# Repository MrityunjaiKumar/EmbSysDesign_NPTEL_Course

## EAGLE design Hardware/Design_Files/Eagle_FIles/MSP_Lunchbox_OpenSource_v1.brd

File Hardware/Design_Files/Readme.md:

# Design Files

- [Eagle Files locations ](./Eagle/)

### Schematic file

### Board file

### License
 GPL-3.0 License

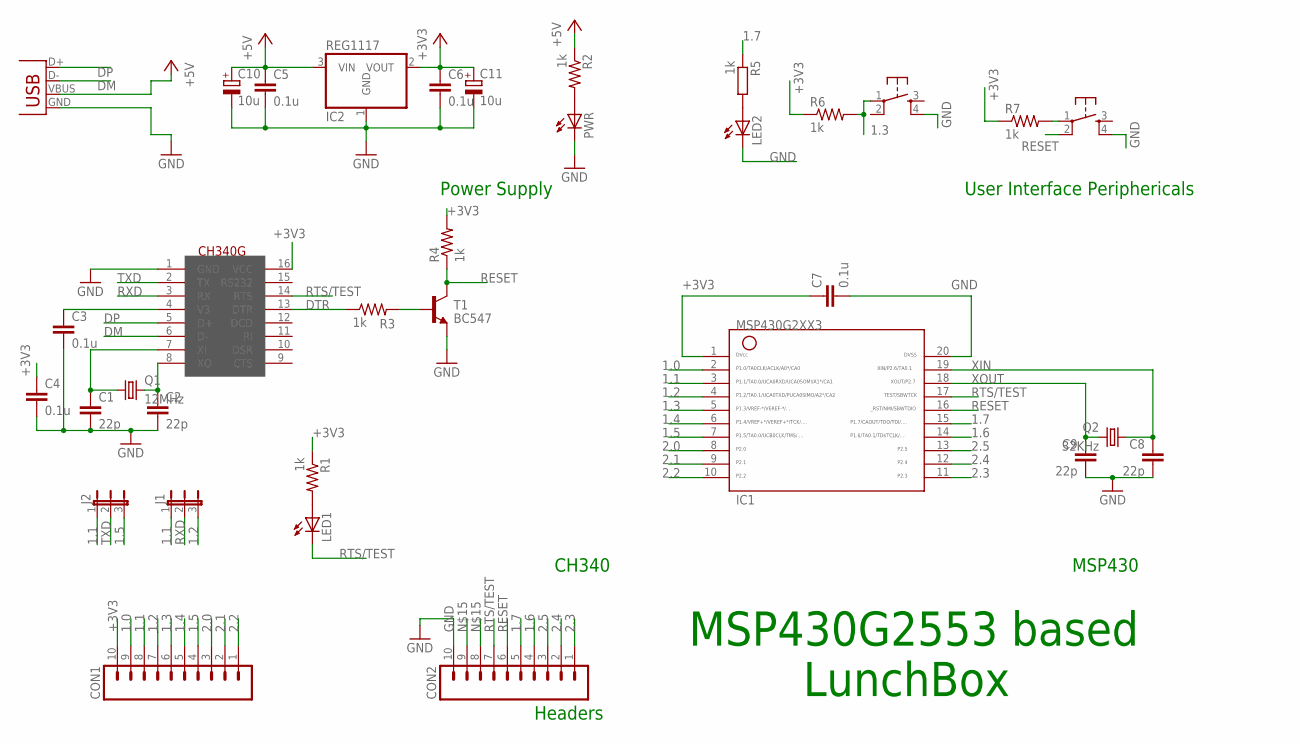
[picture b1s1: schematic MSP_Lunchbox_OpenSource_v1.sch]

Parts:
C1, C2, C8, C9: 22p; C0805
C3, C4, C5, C6: 0.1u; C0805
C7: 0.1u; C075-032X103
C10, C11: 10u; B/3528-21R
CH340: CH340; SOIC16
CON1, CON2: M10; 10P
IC1: MSP430G2553DIP20; G2553-DIP20
IC2: REG1117; SOT223
J1, J2: JP2E; JP2
LED1, LED2: LED3MM
PWR: LED3MM
Q1: 12MHz; HC49US
Q2: 32KHz; TC26H
R1, R2, R3, R4: 1k; 0207/10
R5: 1k; 0207/12
R6, R7: 1k; 0204/7
RESET: OMRON_SWITCH_10-XX; B3F-10XX
SW1: OMRON_SWITCH_10-XX; B3F-10XX
T1: BC547; TO92
X2: USBSMD; USB-MINIB

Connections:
1.0: CON1.9, IC1.2
1.1: CON1.8, IC1.3, J1.1, J2.1
1.2: CON1.7, IC1.4, J1.3
1.3: CON1.6, IC1.5, R6.2, SW1.1
1.4: CON1.5, IC1.6
1.5: CON1.4, IC1.7, J2.3
1.6: CON2.4, IC1.14
1.7: CON2.5, IC1.15, R5.1
2.0: CON1.3, IC1.8
2.1: CON1.2, IC1.9
2.2: CON1.1, IC1.10
2.3: CON2.1, IC1.11
2.4: CON2.2, IC1.12
2.5: CON2.3, IC1.13
+3V3: C4.1, C6.1, C7.1, C11.+, CH340.16 (VCC), CON1.10, IC1.1, IC2.2 (VOUT), R1.1, R4.2, R6.1, R7.1
+5V: C5.1, C10.+, IC2.3 (VIN), R2.1, X2.VBUS
DM: CH340.6 (D-), X2.D-
DP: CH340.5 (D+), X2.D+
DTR: CH340.13 (DTR), R3.1
GND: C1.2, C2.2, C3.2, C4.2, C5.2, C6.2, C7.2, C8.2, C9.2, C10.-, C11.-, CH340.1 (GND), CON2.10, IC1.20, IC2.1 (GND), LED2.K (C), PWR.K (C), RESET.4 (S1), SW1.4 (S1), T1.1 (E), X2.GND
unnamed: LED1.A, R1.2
unnamed: PWR.A, R2.2
unnamed: C1.1, CH340.7 (XI), Q1.1
unnamed: C2.1, CH340.8 (XO), Q1.2
unnamed: LED2.A, R5.2
unnamed: R7.2, RESET.1
unnamed: R3.2, T1.2 (B)
unnamed: C3.1, CH340.4 (V3)
RESET: CON2.6, IC1.16, R4.1, RESET.2 (P1), T1.3 (C)
RTS/TEST: CH340.14 (RTS), CON2.7, IC1.17, LED1.K (C)
RXD: CH340.3 (RX), J1.2
TXD: CH340.2 (TX), J2.2
XIN: C8.1, IC1.19, Q2.1
XOUT: C9.1, IC1.18, Q2.2

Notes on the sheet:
Power Supply
MSP430
Headers
User Interface Periphericals
CH340
MSP430G2553 based
LunchBox

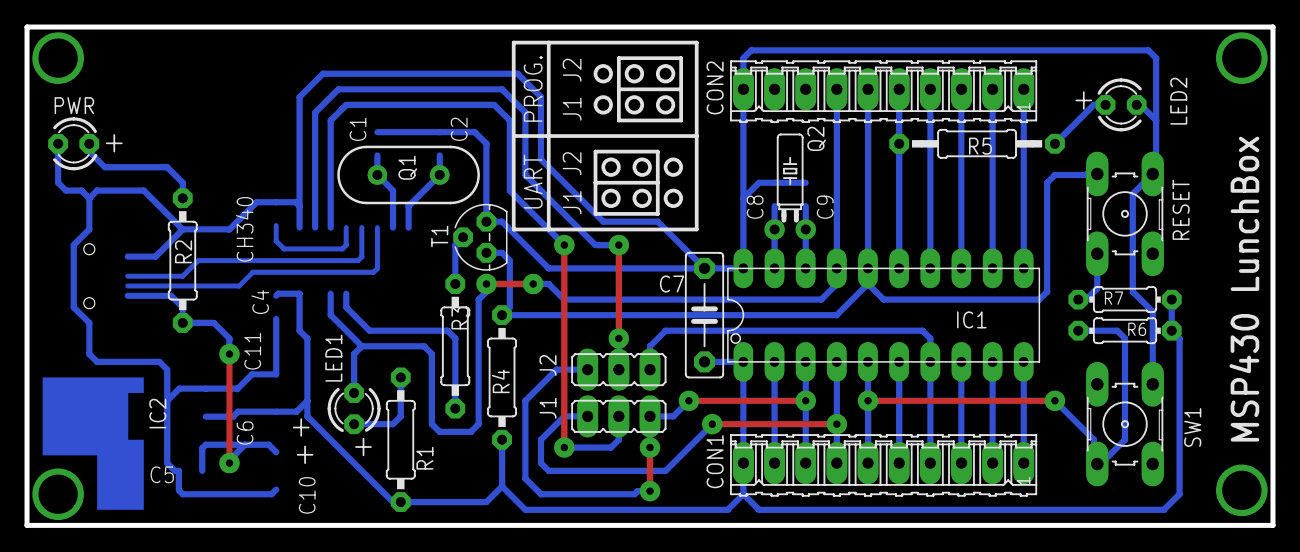
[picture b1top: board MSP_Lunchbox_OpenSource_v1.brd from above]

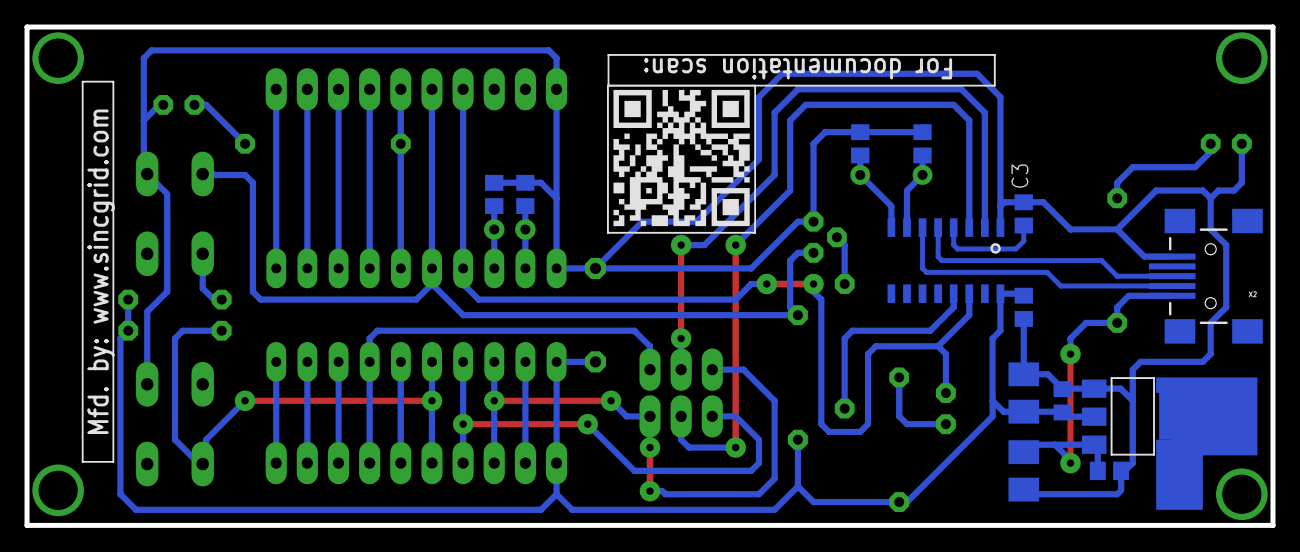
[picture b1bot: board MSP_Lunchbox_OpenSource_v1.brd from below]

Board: 2 copper layers, 101.6 x 40.6 mm, 34 parts (13 on the bottom side), 34 nets.

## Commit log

2020-01-18 Uploaded UART_printf example zip file.
2020-01-20 basic code added
2020-01-20 Exp01_LunchBox_HelloLED
2020-01-20 Exp00_LunchBox_Template
2020-01-20 Exp00_LunchBox_Template readme files added
2020-01-20 Exp02_LunchBox_HelloLED
2020-01-21 few changes
2020-01-21 relative path added in programming stage
2020-01-21 gitignore added updated
2020-01-21 Frtzing parts added
2020-01-21 Exp01_LunchBox_HelloBlink
2020-01-21 Exp01_LunchBox_HelloLED setting changed
2020-01-21 Exp03_LunchBox_HelloSwitch
2020-01-21 Exp04_LunchBox_DebuncingTheSwitch
2020-01-21 Exp05_LunchBox_HelloInterrupt
2020-01-21 Exp06_LunchBox_HelloSSDWithInterrupt
2020-01-21 Exp06_LunchBox_HelloLPM
2020-01-21 Exp06_LunchBox_HelloSoftwarePWM
2020-01-21 Exp06_LunchBox_HelloHardwarePWM
2020-01-21 Exp06_LunchBox_HelloTimer
2020-01-21 Exp06_LunchBox_HelloADC
2020-01-21 Revert "Exp06_LunchBox_HelloADC"
    This reverts commit bf8f5b552d71d1fb053731d9e973f6075959c436.
2020-01-22 Exp11_LunchBox_HelloADC
2020-01-22 Revert "Exp06_LunchBox_HelloTimer"
    This reverts commit 1a618a842961dcd59d66d6eee8575db25c5fa477.
2020-01-22 Exp12_LunchBox_RefreshSSD
2020-01-22 Exp13_LunchBox_HelloSerial
2020-01-22 Exp14_LunchBox_HelloTouch
2020-01-22 Exp15_LunchBox_HelloLCD
2020-01-22 Exp16_LunchBox_Hello555
2020-01-22 Exp17_LunchBox_HelloClock
2020-01-22 Exp10_LunchBox_HelloTimer
2020-01-25 Updated Exp01_LunchBox_HelloLED.c according to LunchBox LED
2020-01-25 Updated Exp02_LunchBox_HelloBlink.c according to LunchBox LED
2020-01-25 Updated Exp03_LunchBox_HelloSwitch.c according to LunchBox LED and Switch
2020-01-25 Updated Exp03_LunchBox_HelloSwitch.c comments
2020-01-25 Updated Exp04_LunchBox_DebouncingTheSwitch.c according to LunchBox LED and Switch
2020-01-25 Updated Exp05_LunchBox_HelloInterrupt.c according to LunchBox LED and Switch
2020-01-25 Updated Exp05_LunchBox_HelloSSDWithInterrupt.c, changes left
2020-01-25 Updated Exp05_LunchBox_HelloInterrupt.c according to LunchBox LED and Switch with comments
2020-01-25 Updated Exp06_LunchBox_HelloSSDWithInterrupt.c with comments, changes left
2020-01-28 Exp08_LunchBox_HelloSoftwarePWM according to LunchBox
2020-01-29 Exp1_LunchBox_HelloLED settings update
2020-01-29 Exp02_LunchBox_HelloBlink settings update
2020-01-29 Exp11_LunchBox_HelloADC final commit
2020-01-29 Exp09_LunchBox_HelloHardwarePWM final commit
2020-01-29 Properties Setting changed
2020-01-29 Exp06_LunchBox_HelloSSDWithInterrupt final commit
2020-01-29 Exp13_LunchBox_HelloSerial final commit
2020-01-29 Exp13_LunchBox_HelloSerial comment changes
2020-01-29 Exp15_LunchBox_HelloLCD Final Commit
2020-01-29 Exp12_LunchBox_RefreshSSD Final Commit
2020-01-29 Exp11_LunchBox_HelloADC changed pin
2020-01-30 Exp16_LunchBox_Hello555 final commit
2020-01-30 Exp07_LunchBox_HelloLPM final commit
2020-01-30 Exp05_LunchBox_HelloInterrupt comment update
2020-01-30 Exp17_LunchBox_HelloClock final commit
2020-02-03 fritzing image updated
2020-02-09 Ch340_driver added
2020-02-10 Changed code numbering
2020-02-10 Updated Readme.md of some Experiments from Exp00 to Exp06
2020-02-11 Changed exercise numbering
2020-02-12 gist added for documentation
2020-02-14 Added Gist.rst file
2020-02-15 Updated Hello Timer code
2020-02-15 Updated Refresh SSD code
2020-02-16 Changed Hello SSD code
2020-02-16 Updated Hello_LPM code
2020-02-16 Changed Name of Hello SSD folder
2020-02-16 Updated Hello SSD
2020-02-17 Updated Hello SSD code
2020-02-18 Exp07_LunchBox_HelloClock updated
2020-02-18 Exp07_LunchBox_HelloResetSource updated
2020-02-18 Updated Hello Reset Source code
2020-02-18 HelloClock code changed
2020-02-19 HelloClock code updated
2020-02-19 Updated Hello Clock code
2020-02-19 Updated HelloResetSource code
2020-02-21 Updated Hello LCD code
2020-02-21 Added New LCD code and renamed other
2020-02-21 Updated LCD codes
2020-02-22 Updated Hello Software PWM code
2020-02-25 Added testing codes
2020-02-25 Updated comments in Exp18_LunchBox_HelloSerial.c
2020-02-26 Updated TimerCapture codes
2020-02-26 Added Hello DAC
2020-02-26 Updated Hello Hardware PWM 8 bit PWM
2020-02-26 Updated Hello Hardware 16 bit PWM
2020-02-26 Updated Hello Serial
2020-02-26 Added Lemon Battery LED Blink
2020-02-26 Added Hello Software PWM with Large Delay
2020-02-26 Finalized HelloPeriod
2020-02-26 Finalized Frequency measurement codes
2020-02-27 uart example and embedded c uploaded
2020-02-27 Added Refresh SSD codes
2020-03-02 Modified HelloPeriod code
2020-03-04 Modified comments
2020-03-04 CharlieLog code pushed
2020-03-06 Added SerialLog code
2020-03-06 Updated Ex23 comments code
2020-03-06 Updated Exp00 setting
2020-03-06 Test file
2020-03-25 Added Readme file
2020-03-25 Template files updated
2020-03-25 Digital IO codes updated
2020-03-25 Digital IO: Switch Interfacing codes updated
2020-03-25 Clock System and Reset codes updated
2020-03-25 Interrupts in MSP430 codes updated
2020-03-25 Single SSD and LPM in MSP430 codes updated
2020-03-25 16*2 LCD codes updated
2020-03-25 Timer (Basics and Compare Mode) codes updated
2020-03-25 Timer (PWM) codes updated
2020-03-25 ADC in MSP430 codes updated
2020-03-25 ADC(LFSR) and DAC codes updated
2020-03-25 Serial Communication Codes updated
2020-03-25 Timer(Capture Mode) Codes updated
2020-03-25 Coding Ninja Codes updated
2020-05-20 NinjaLevel_EmbeddedC
2020-05-22 Demo of readme
    Please remove afterwards
2020-06-12 Design files added
2020-06-12 spell corrected
2020-06-12 lanidng readme updated
2020-06-12 readme updated
2020-06-12 Changed Readme file
2020-06-14 gist modified
2020-06-15 synced wrt documentation
2020-06-15 Updated Readme and gist
2020-09-15 Create LICENSE
2020-09-15 Update LICENSE

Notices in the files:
parts and their libraries:
SparkFun-Aesthetics: Licensing: Creative Commons ShareAlike 4.0 International - https://creativecommons.org/licenses/by-sa/4.0
